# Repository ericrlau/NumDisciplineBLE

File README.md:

# nRFMicro
BLE board to replace the ATMEGA32A-PU used on the NumDiscipline (https://github.com/ericrlau/NumDisciplineBLE)

Based on the work of joric and the nrfMicro - Project wiki: https://github.com/joric/nrfmicro/wiki

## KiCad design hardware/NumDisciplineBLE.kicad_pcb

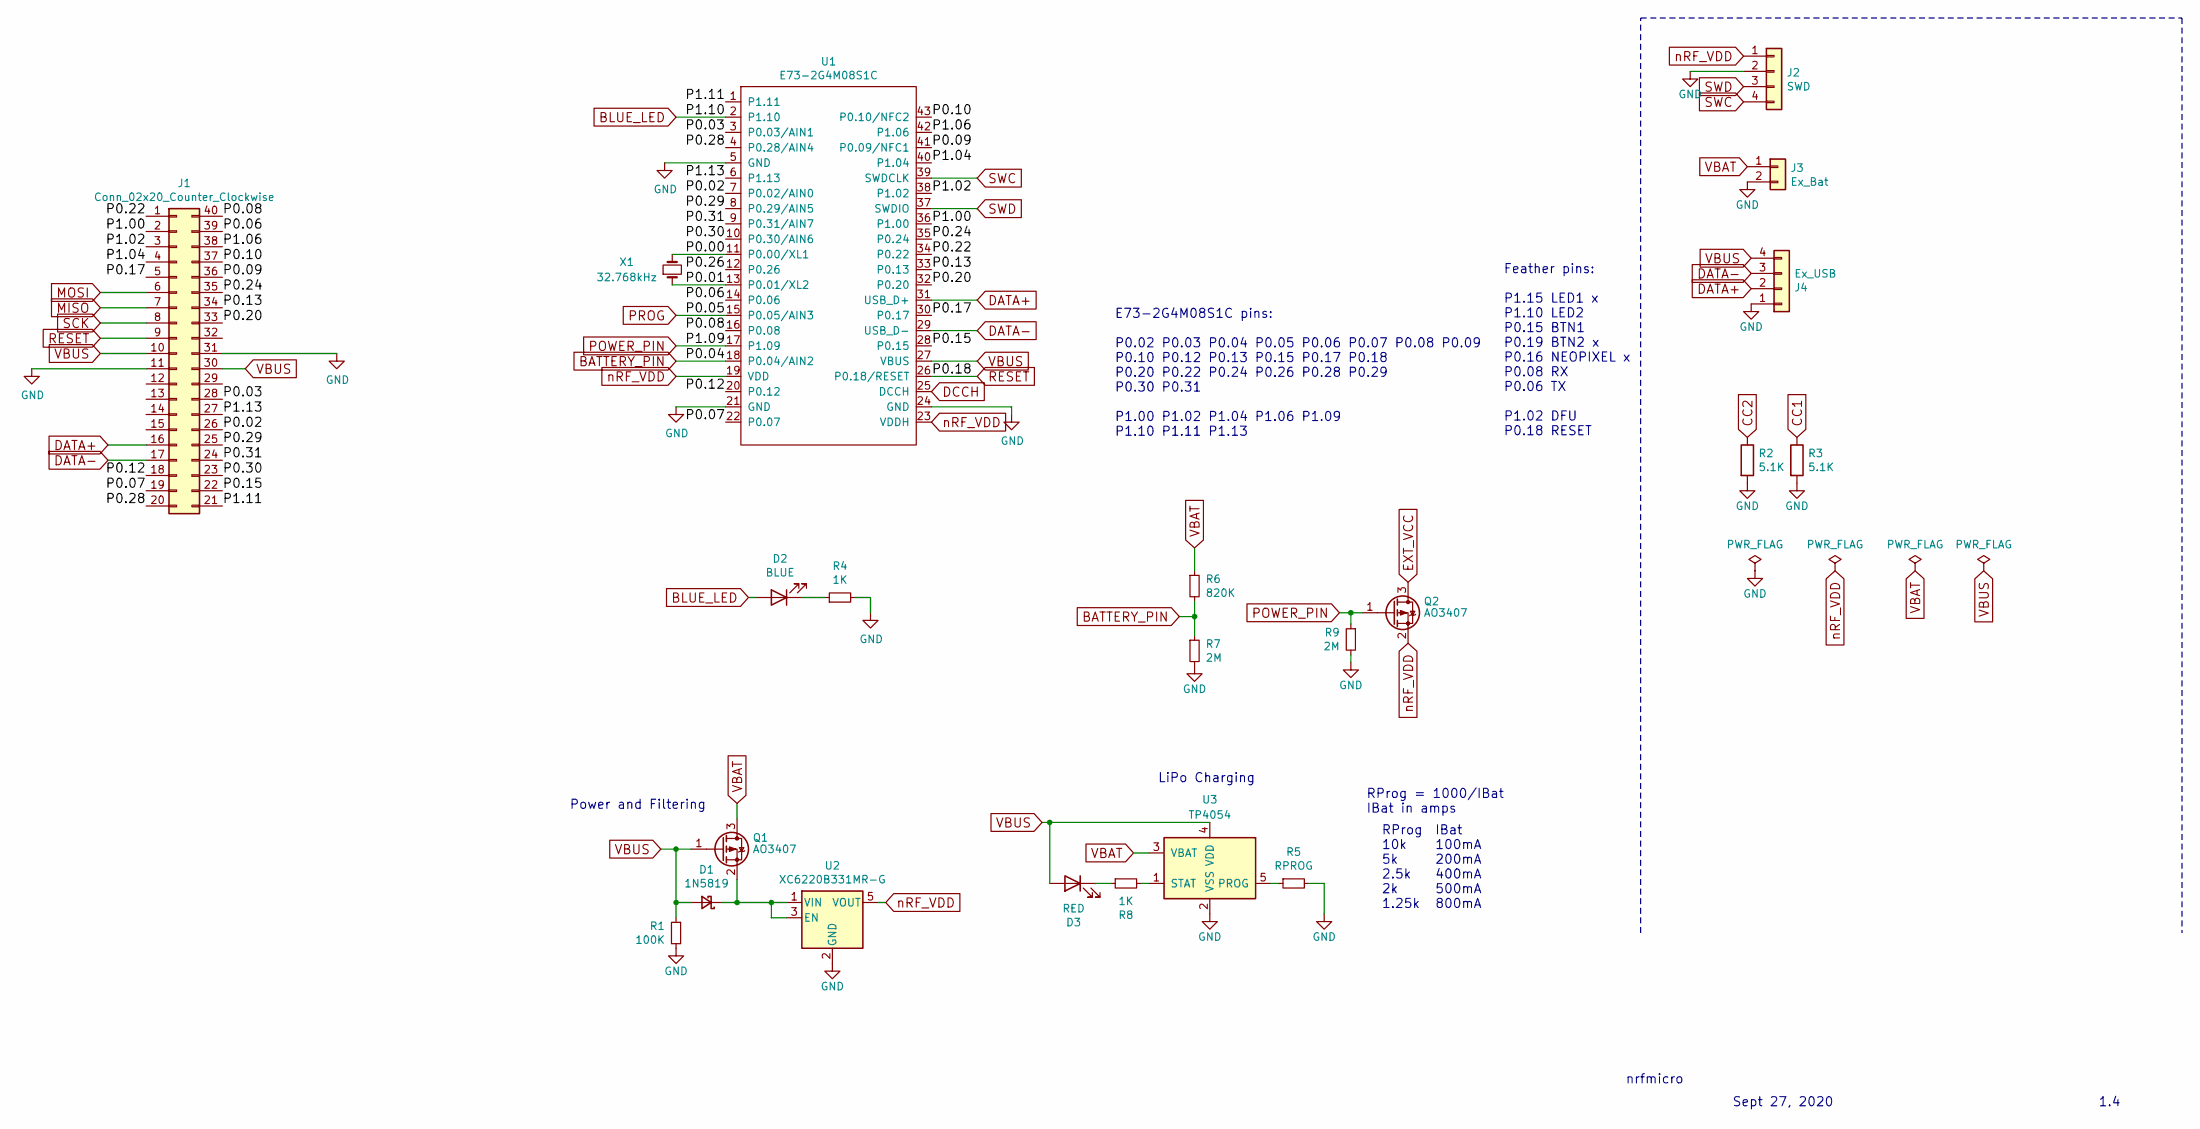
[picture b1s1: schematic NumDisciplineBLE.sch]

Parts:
D1: 1N5819; D_SOD-323F
D2: BLUE; LED_0603_1608Metric
D3: RED; LED_0603_1608Metric
J1: Conn_02x20_Counter_Clockwise; 2x20_P2.54mm_Vertical_SMD_reversed
J2: SWD; connector_swd
J3: Ex_Bat; connector_bat
J4: Ex_USB; connector_usb
Q1, Q2: AO3407; SOT-23
R1: 100K; R_0603_1608Metric
R2, R3: 5.1K; R_0603_1608Metric
R4, R8: 1K; R_0603_1608Metric
R5: RPROG; R_0603_1608Metric
R6: 820K; R_0603_1608Metric
R7, R9: 2M; R_0603_1608Metric
U1: E73-2G4M08S1C; E73-2G4M08S1C-52840
U2: XC6220B331MR-G; SOT-23-5
U3: TP4054; SOT-23-5
X1: 32.768kHz; Crystal_SMD_MicroCrystal_CM9V-T1A-2Pin_1.6x1.0mm

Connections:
/P0.00: U1.11 (P0.00/XL1), X1.2
/P0.01: U1.13 (P0.01/XL2), X1.1
/P0.02: J1.26, U1.7 (P0.02/AIN0)
/P0.03: J1.28, U1.3 (P0.03/AIN1)
/P0.06: J1.39, U1.14 (P0.06)
/P0.07: J1.19, U1.22 (P0.07)
/P0.08: J1.40, U1.16 (P0.08)
/P0.09: J1.36, U1.41 (P0.09/NFC1)
/P0.10: J1.37, U1.43 (P0.10/NFC2)
/P0.12: J1.18, U1.20 (P0.12)
/P0.13: J1.34, U1.33 (P0.13)
/P0.15: J1.22, U1.28 (P0.15)
/P0.17: J1.5, U1.30 (P0.17)
/P0.20: J1.33, U1.32 (P0.20)
/P0.22: J1.1, U1.34 (P0.22)
/P0.24: J1.35, U1.35 (P0.24)
/P0.26: U1.12 (P0.26)
/P0.28: J1.20, U1.4 (P0.28/AIN4)
/P0.29: J1.25, U1.8 (P0.29/AIN5)
/P0.30: J1.23, U1.10 (P0.30/AIN6)
/P0.31: J1.24, U1.9 (P0.31/AIN7)
/P1.00: J1.2, U1.36 (P1.00)
/P1.02: J1.3, U1.38 (P1.02)
/P1.04: J1.4, U1.40 (P1.04)
/P1.06: J1.38, U1.42 (P1.06)
/P1.11: J1.21, U1.1 (P1.11)
/P1.13: J1.27, U1.6 (P1.13)
BATTERY_PIN: R6.2, R7.1, U1.18 (P0.04/AIN2)
BLUE_LED: D2.2 (A), U1.2 (P1.10)
DATA+: J1.16, J4.2, U1.31 (USB_D+)
DATA-: J1.17, J4.3, U1.29 (USB_D-)
DCCH: U1.25 (DCCH)
EXT_VCC: Q2.3 (D)
GND: J1.11, J1.31, J2.2, J3.2, J4.1, R1.2, R2.2, R3.2, R4.2, R5.2, R7.2, R9.2, U1.5 (GND), U1.21 (GND), U1.24 (GND), U2.2 (GND), U3.2 (VSS)
MISO: J1.7
MOSI: J1.6
unnamed: D1.1 (K), Q1.2 (S), U2.1 (VIN), U2.3 (EN)
unnamed: D2.1 (K), R4.1
unnamed: D3.1 (K), R8.1
unnamed: R5.1, U3.5 (PROG)
unnamed: R8.2, U3.1 (STAT)
POWER_PIN: Q2.1 (G), R9.1, U1.17 (P1.09)
PROG: U1.15 (P0.05/AIN3)
RESET: J1.9, U1.26 (P0.18/RESET)
SCK: J1.8
SWC: J2.4, U1.39 (SWDCLK)
SWD: J2.3, U1.37 (SWDIO)
VBAT: J3.1, Q1.3 (D), R6.1, U3.3 (VBAT)
VBUS: D1.2 (A), D3.2 (A), J1.10, J1.30, J4.4, Q1.1 (G), R1.1, U1.27 (VBUS), U3.4 (VDD)
nRF_VDD: J2.1, Q2.2 (S), U1.19 (VDD), U1.23 (VDDH), U2.5 (VOUT)

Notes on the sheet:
nrfmicro
Sept 27, 2020
1.4
E73-2G4M08S1C pins: P0.02 P0.03 P0.04 P0.05 P0.06 P0.07 P0.08 P0.09 P0.10 P0.12 P0.13 P0.15 P0.17 P0.18 P0.20 P0.22 P0.24 P0.26 P0.28 P0.29 P0.30 P0.31 P1.00 P1.02 P1.04 P1.06 P1.09 P1.10 P1.11 P1.13
Feather pins: P1.15 LED1 x P1.10 LED2 P0.15 BTN1 P0.19 BTN2 x P0.16 NEOPIXEL x P0.08 RX P0.06 TX P1.02 DFU P0.18 RESET
Power and Filtering
LiPo Charging
RProg 10k 5k 2.5k 2k 1.25k
IBat 100mA 200mA 400mA 500mA 800mA
RProg = 1000/IBat IBat in amps

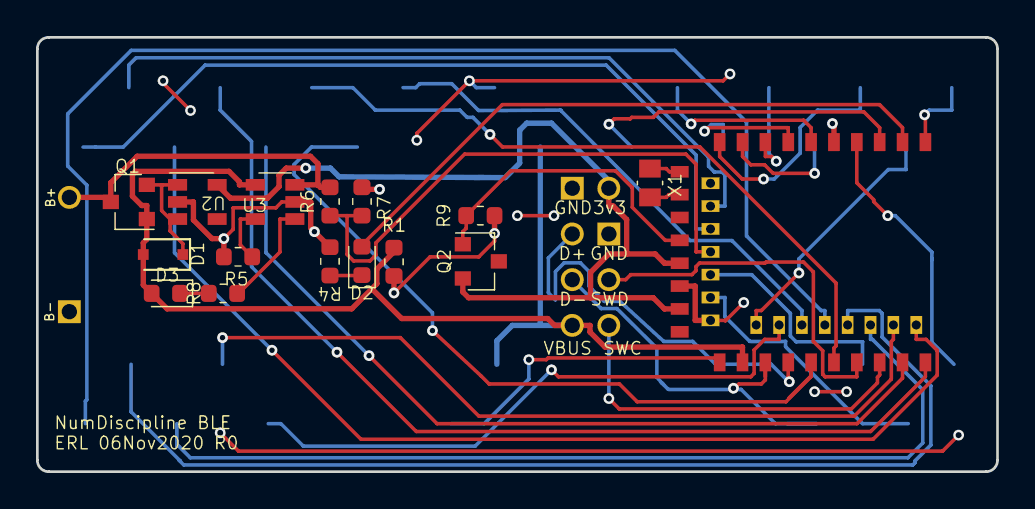
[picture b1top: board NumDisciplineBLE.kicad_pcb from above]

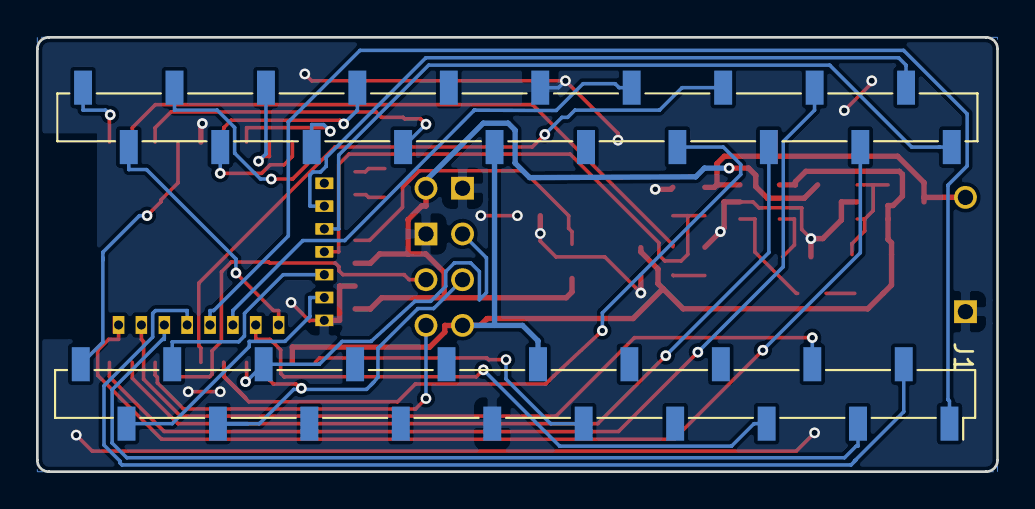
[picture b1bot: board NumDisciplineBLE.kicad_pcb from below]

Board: 2 copper layers, 53.3 x 24.1 mm, 20 parts (3 on the bottom side), 43 nets.

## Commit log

2020-11-01 initial, nrfMicro files
2020-11-01 starting to modify, lots to do still
2020-11-02 add 40 pin header, about to delete atmega
2020-11-03 basic layout done
2020-11-03 pre-routing
2020-11-03 pre-routing2
2020-11-03 post-autoroute
2020-11-04 first gerbers
2020-11-07 R0 done
